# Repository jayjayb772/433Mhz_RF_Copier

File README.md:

# 433Mhz_RF_Copier
This is an arduino sketch that uses an esp8266, oled display, and 433Mhz receiver and transmitter to record and playback 433Mhz signals

## Install Required Libraries in Arduino IDE
In your Arduino IDE, on the top left select `Sketch->Include Library->Manage Libraries`
Once in the Library Manager search for and install the following Libraries:
- rc-switch by sui77, fingolfin
- Adafruit SSD1306 by Adafruit
  - This should automatically install the Adafruit GFX Library as well

## Configure code for your own build

### EEPROM Size

### Button Pins

### Reciever and Transmitter Pins

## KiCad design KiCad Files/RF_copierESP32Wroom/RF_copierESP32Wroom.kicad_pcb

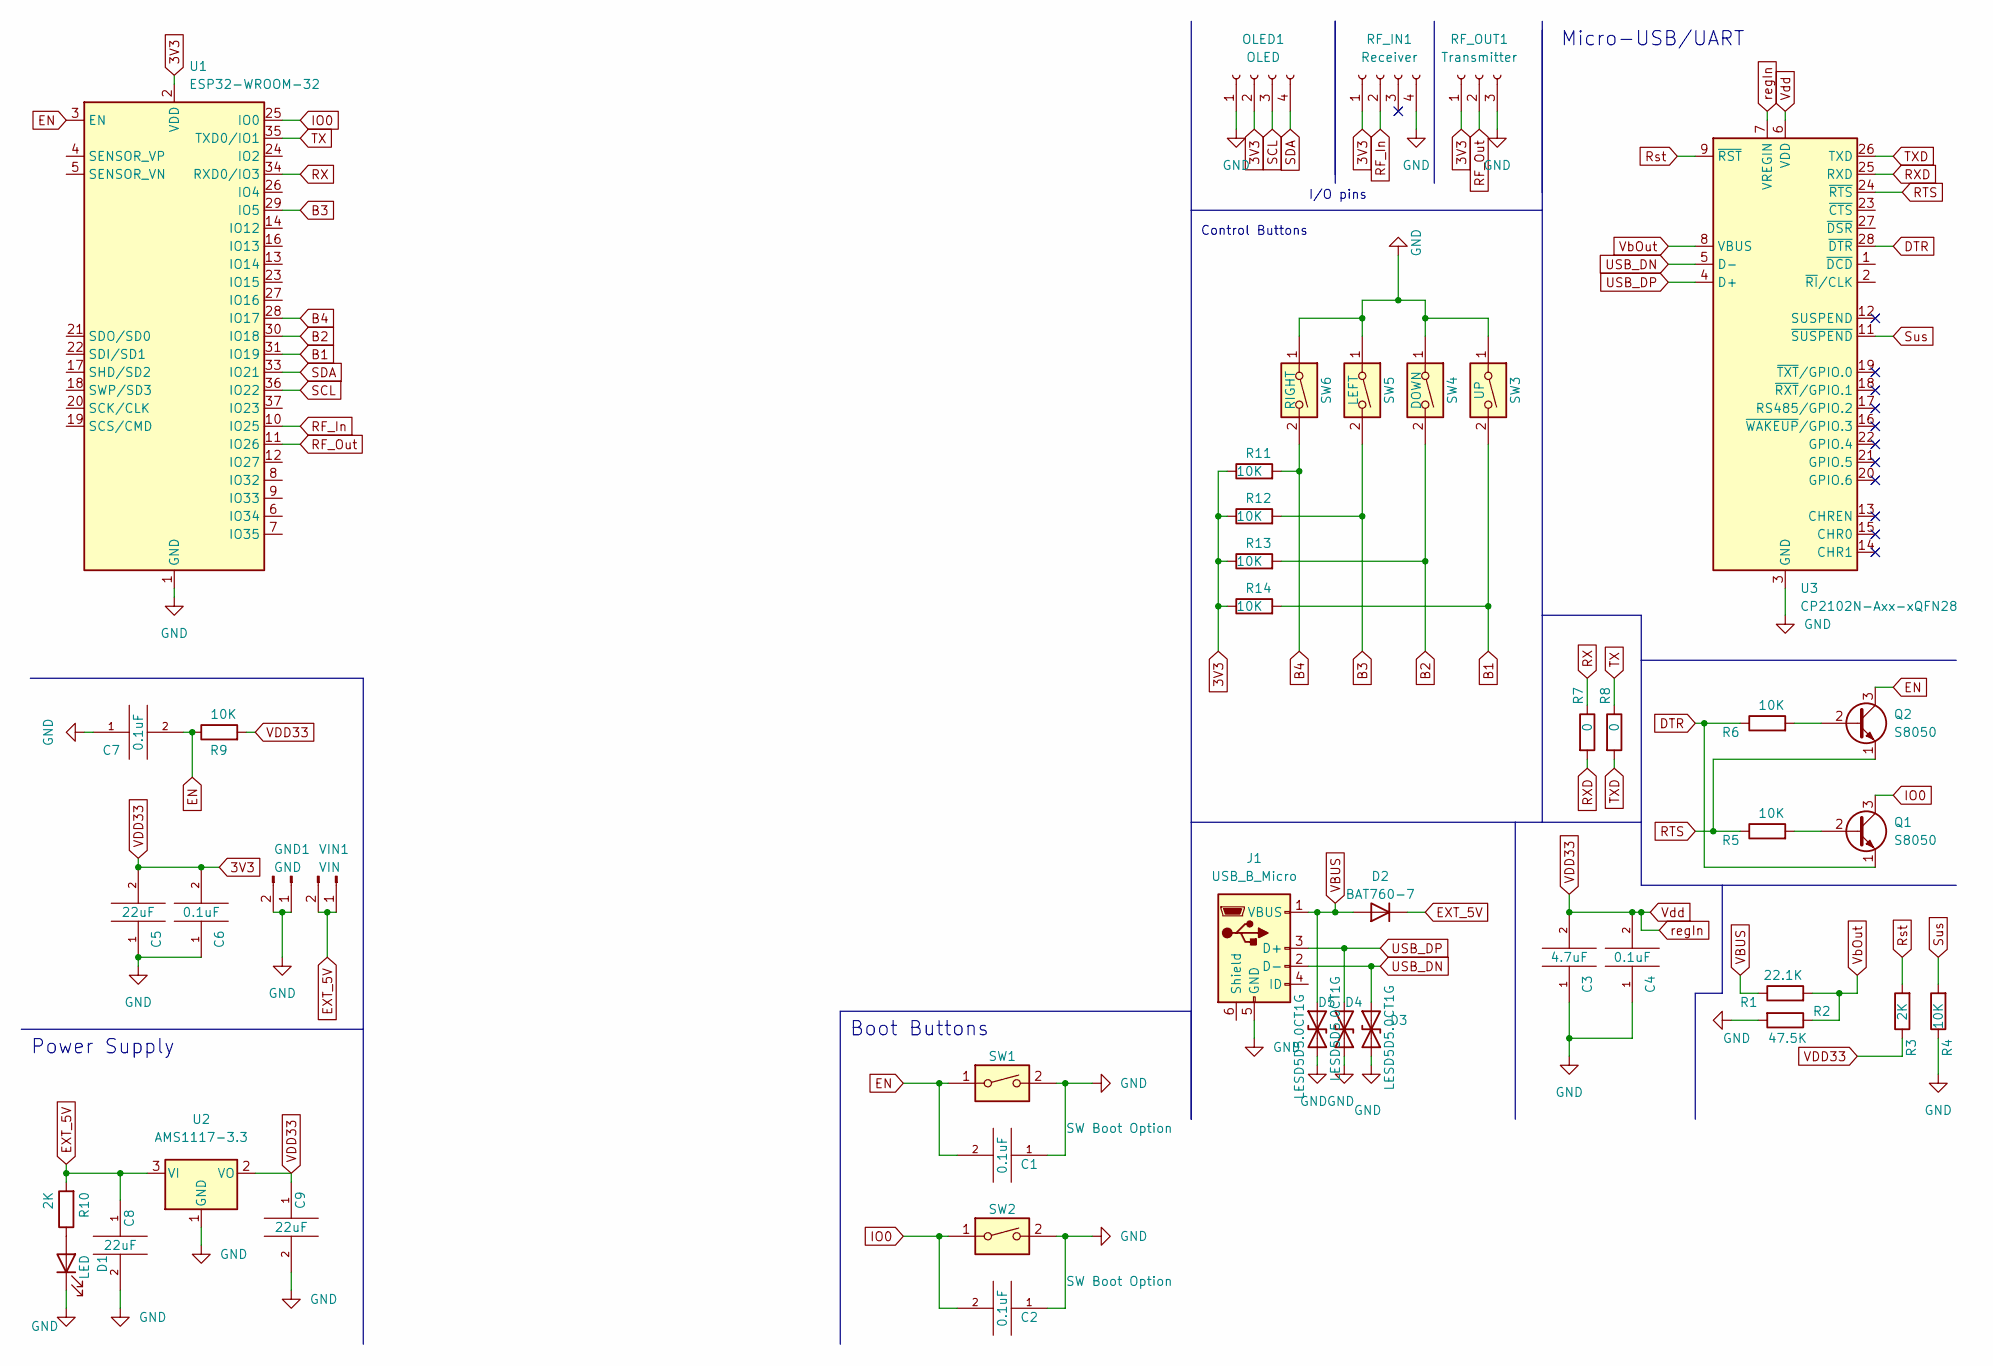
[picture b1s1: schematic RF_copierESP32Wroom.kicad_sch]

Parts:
C1, C2, C4, C6, C7: 0.1uF; C_0201_0603Metric_Pad0.64x0.40mm_HandSolder
C3: 4.7uF; C_0201_0603Metric_Pad0.64x0.40mm_HandSolder
C5, C8, C9: 22uF; C_0201_0603Metric_Pad0.64x0.40mm_HandSolder
D1: LED; D_1206_3216Metric_Pad1.42x1.75mm_HandSolder
D2: BAT760-7; D_SOD-323
D3, D4, D5: LESD5D5.0CT1G; D_SOD-523
GND1: GND; PinSocket_1x02_P2.54mm_Vertical
J1: USB_B_Micro; USB_Micro-B_Amphenol_10118194_Horizontal
OLED1: OLED; PinSocket_1x04_P2.54mm_Vertical
Q1, Q2: S8050; TO-92_Inline
R1: 22.1K; R_0201_0603Metric
R2: 47.5K; R_0201_0603Metric
R3, R10: 2K; R_0201_0603Metric
R4, R5, R6, R9, R11, R12, R13, R14: 10K; R_0201_0603Metric
R7, R8: 0; R_0201_0603Metric
RF_IN1: Receiver; PinSocket_1x04_P2.54mm_Vertical
RF_OUT1: Transmitter; PinSocket_1x03_P2.54mm_Vertical
SW1, SW2: SW Boot Option; SW_Push_1P1T_NO_6x6mm_H9.5mm
SW3: UP; SW_Push_1P1T_NO_6x6mm_H9.5mm
SW4: DOWN; SW_Push_1P1T_NO_6x6mm_H9.5mm
SW5: LEFT; SW_Push_1P1T_NO_6x6mm_H9.5mm
SW6: RIGHT; SW_Push_1P1T_NO_6x6mm_H9.5mm
U1: ESP32-WROOM-32
U2: AMS1117-3.3; SOT-223-3_TabPin2
U3: CP2102N-Axx-xQFN28; QFN-28-1EP_5x5mm_P0.5mm_EP3.35x3.35mm
VIN1: VIN; PinSocket_1x02_P2.54mm_Vertical

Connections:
3V3: C3.2, C4.2, C5.2, C6.2, C9.1, OLED1.2, R3.1, R9.2, R11.1, R12.1, R13.1, R14.1, RF_IN1.1, RF_OUT1.1, U1.2 (VDD), U2.2 (VO), U3.6 (VDD), U3.7 (VREGIN)
B1: R14.2, SW3.2, U1.31 (IO19)
B2: R13.2, SW4.2, U1.30 (IO18)
B3: R12.2, SW5.2, U1.29 (IO5)
B4: R11.2, SW6.2, U1.28 (IO17)
DTR: Q1.1 (E), R6.1, U3.28 (~DTR)
EN: C1.2, C7.2, Q2.3 (C), R9.1, SW1.1, U1.3 (EN)
EXT_5V: C8.1, D2.1 (K), R10.2, U2.3 (VI), VIN1.1, VIN1.2
GND: C1.1, C2.1, C3.1, C4.1, C5.1, C6.1, C7.1, C8.2, C9.2, D1.1 (K), D3.1 (A1), D4.1 (A1), D5.1 (A1), GND1.1, GND1.2, J1.5 (GND), OLED1.1, R2.2, R4.1, RF_IN1.4, RF_OUT1.3, SW1.2, SW2.2, SW3.1, SW4.1, SW5.1, SW6.1, U1.1 (GND), U1.15 (GND), U1.38 (GND), U1.39 (GND), U2.1 (GND), U3.3 (GND), U3.29 (GND)
IO0: C2.2, Q1.3 (C), SW2.1, U1.25 (IO0)
unnamed: D1.2 (A), R10.1
unnamed: Q1.2 (B), R5.2
unnamed: Q2.2 (B), R6.2
RF_In: RF_IN1.2, U1.10 (IO25)
RF_Out: RF_OUT1.2, U1.11 (IO26)
RTS: Q2.1 (E), R5.1, U3.24 (~RTS)
RX: R7.1, U1.34 (RXD0/IO3)
RXD: R7.2, U3.25 (RXD)
Rst: R3.2, U3.9 (~RST)
SCL: OLED1.3, U1.36 (IO22)
SDA: OLED1.4, U1.33 (IO21)
Sus: R4.2, U3.11 (~SUSPEND)
TX: R8.1, U1.35 (TXD0/IO1)
TXD: R8.2, U3.26 (TXD)
USB_DN: D3.2 (A2), J1.2 (D-), U3.5 (D-)
USB_DP: D4.2 (A2), J1.3 (D+), U3.4 (D+)
VBUS: D2.2 (A), D5.2 (A2), J1.1 (VBUS), R1.1
VbOut: R1.2, R2.1, U3.8 (VBUS)

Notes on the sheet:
Micro-USB/UART
Power Supply
Boot Buttons
Control Buttons
I/O pins

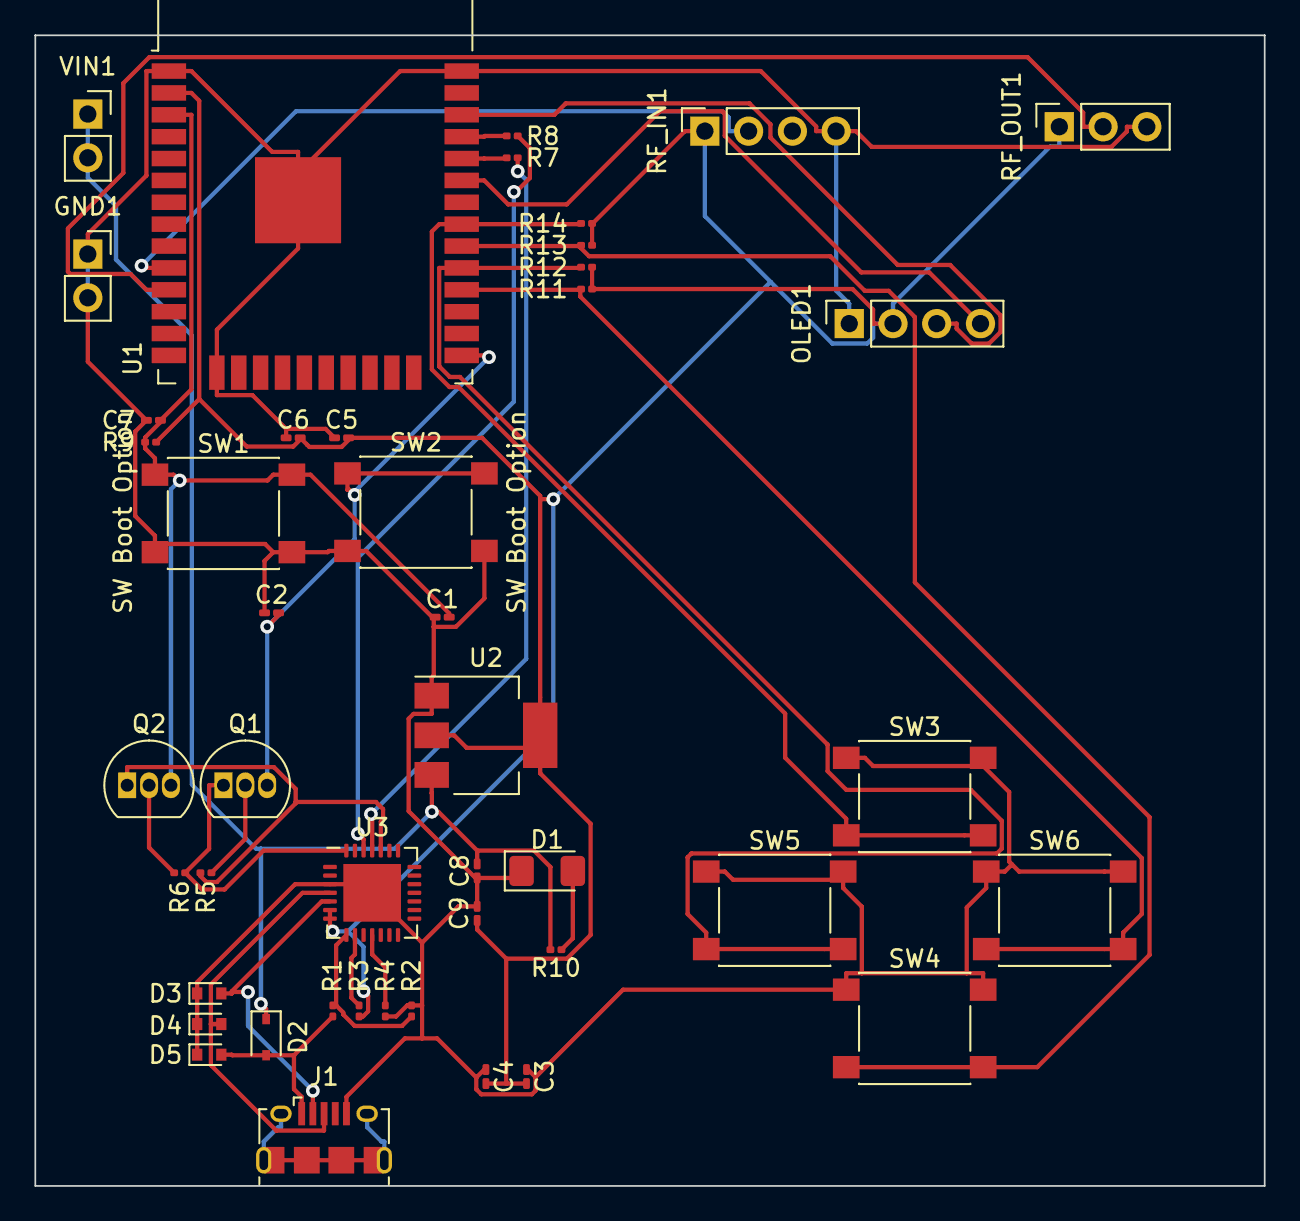
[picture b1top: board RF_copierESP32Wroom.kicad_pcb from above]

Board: 2 copper layers, 71.4 x 66.8 mm, 45 parts (0 on the bottom side), 28 nets.

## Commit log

2022-08-18 Initial Commit of the arduino file
2022-08-18 renamed file so arduino IDE is happy
2022-08-25 Finished code development
2022-09-02 Added Kicad files for my basic pcb
2022-09-02 added bettery charger and footprints
